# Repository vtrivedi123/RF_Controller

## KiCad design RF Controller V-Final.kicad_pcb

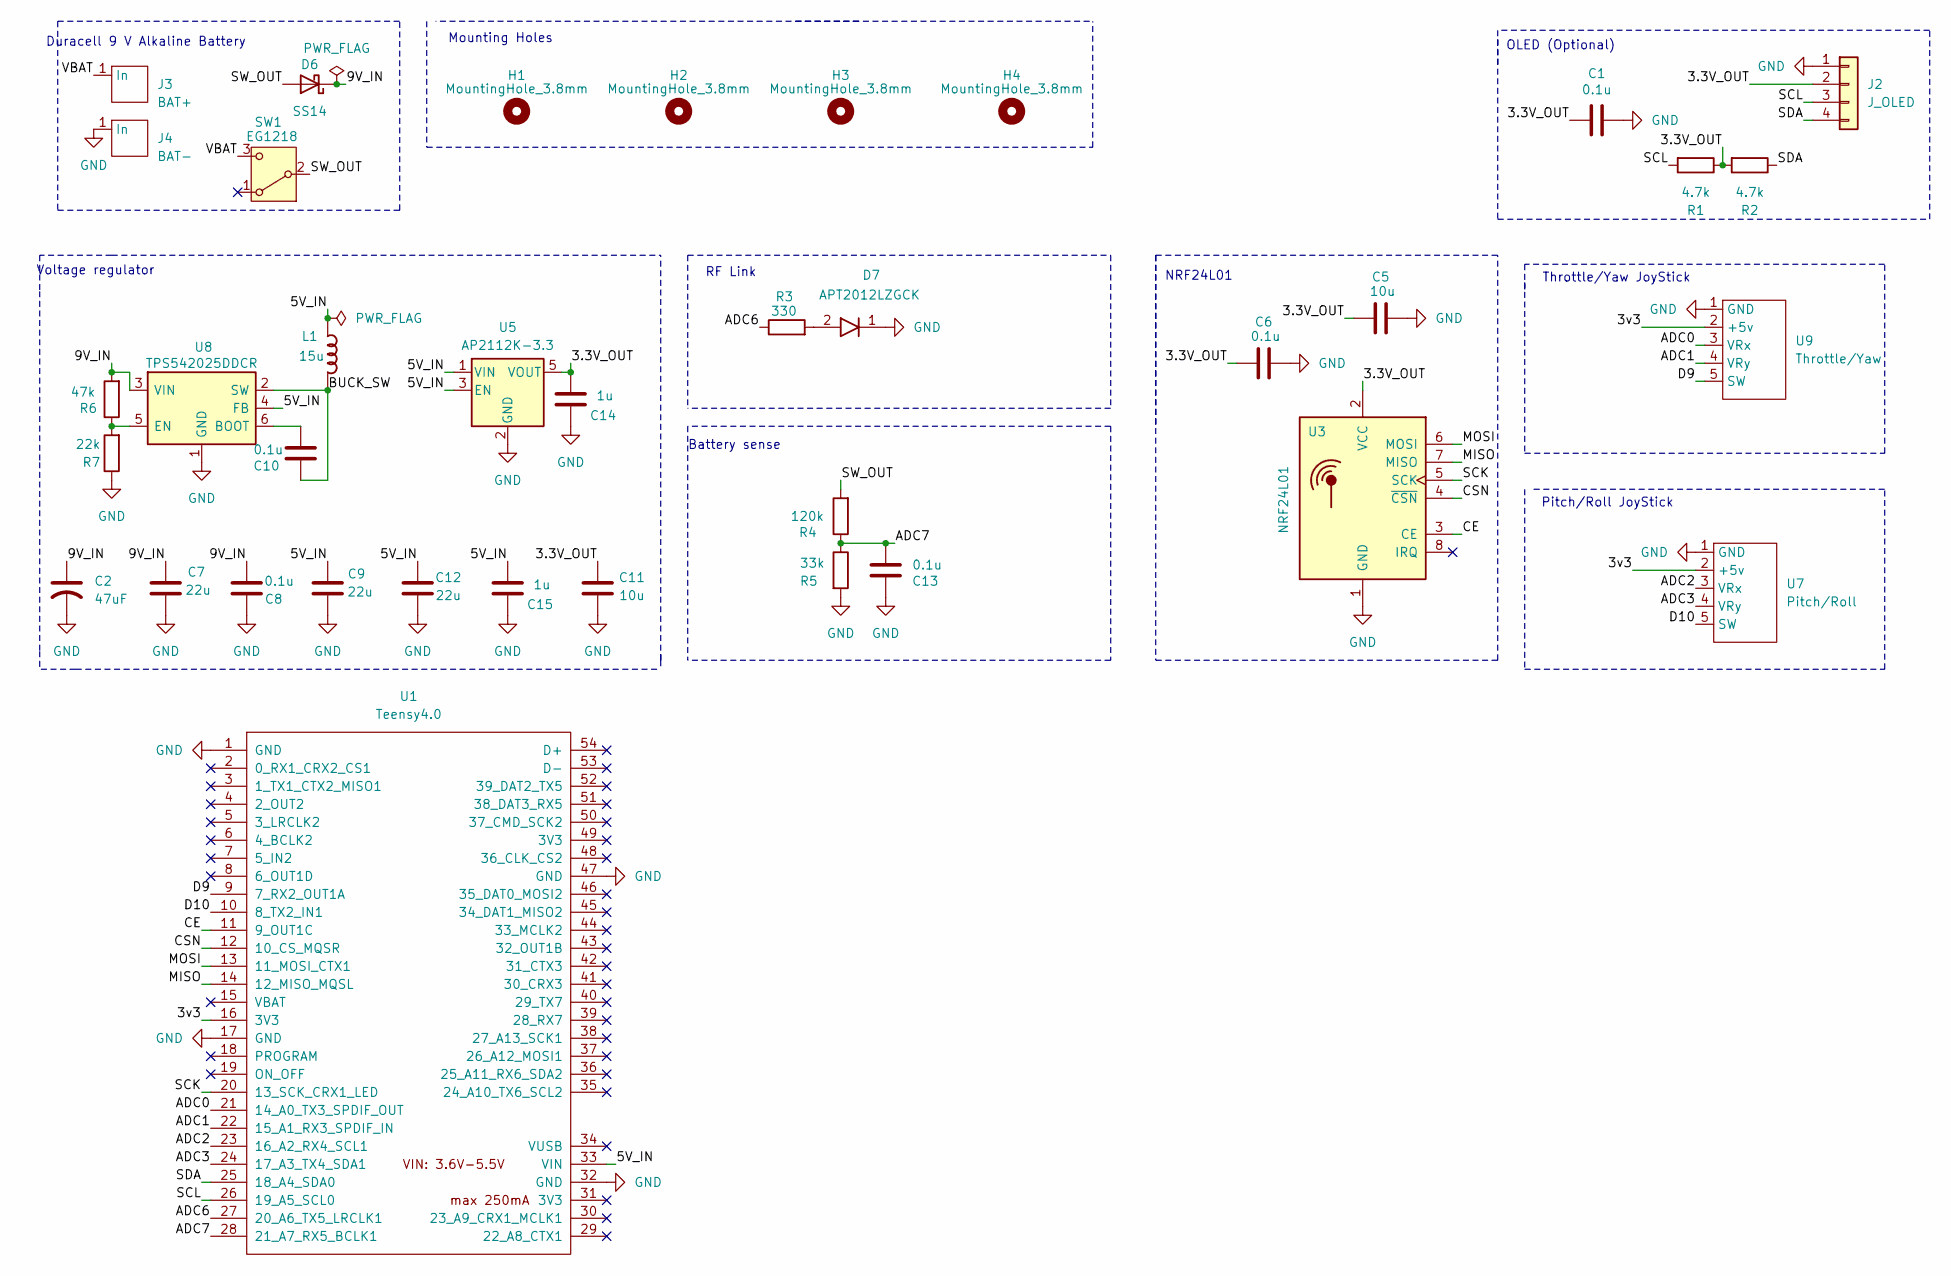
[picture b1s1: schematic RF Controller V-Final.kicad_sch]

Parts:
C1, C6, C8, C10, C13: 0.1u; C_0805_2012Metric_Pad1.18x1.45mm_HandSolder
C2: 47uF; CP_Wurth_WCAP-ASLI-D6.3L5.5
C5, C11: 10u; C_1206_3216Metric_Pad1.33x1.80mm_HandSolder
C7, C9, C12: 22u; C_1210_3225Metric_Pad1.33x2.70mm_HandSolder
C14, C15: 1u; C_0805_2012Metric_Pad1.18x1.45mm_HandSolder
D6: SS14; D_SMA
D7: APT2012LZGCK; LED_0805_2012Metric_Pad1.15x1.40mm_HandSolder
H1, H2, H3, H4: MountingHole_3.8mm
J2: J_OLED; OLED_0.96in_SSD1306_I2C_27x27mm_TOP_HEADER_SIMPLE
J3: BAT+; Pad_01
J4: BAT-; Pad_01
L1: 15u; Bourns_SRP5030HMCT
R1, R2: 4.7k; R_0805_2012Metric_Pad1.20x1.40mm_HandSolder
R3: 330; R_0805_2012Metric_Pad1.20x1.40mm_HandSolder
R4: 120k; R_0805_2012Metric_Pad1.20x1.40mm_HandSolder
R5: 33k; R_0805_2012Metric_Pad1.20x1.40mm_HandSolder
R6: 47k; R_0805_2012Metric_Pad1.20x1.40mm_HandSolder
R7: 22k; R_0805_2012Metric_Pad1.20x1.40mm_HandSolder
SW1: EG1218; SW_ES_EG1218
U1: Teensy4.0; Teensy40
U3: NRF24L01; nRF24L01_Breakout
U5: AP2112K-3.3; SOT-23-5
U7: Pitch/Roll; JOY1
U8: TPS542025DDCR; TSOT-23-6_HandSoldering
U9: Throttle/Yaw; JOY1

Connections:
/3.3V_OUT: C1.1, C5.1, C6.1, C11.1, C14.1, J2.2, R1.1, R2.2, U3.2 (VCC), U5.5 (VOUT)
/3v3: U1.16 (3V3), U7.2 (+5v), U9.2 (+5v)
/5V_IN: C9.1, C12.1, C15.2, L1.2, U1.33 (VIN), U5.1 (VIN), U5.3 (EN), U8.4 (FB)
/9V_IN: C2.1, C7.1, C8.2, D6.1 (K), R6.2, U8.3 (VIN)
/ADC0: U1.21 (14_A0_TX3_SPDIF_OUT), U9.3 (VRx)
/ADC1: U1.22 (15_A1_RX3_SPDIF_IN), U9.4 (VRy)
/ADC2: U1.23 (16_A2_RX4_SCL1), U7.3 (VRx)
/ADC3: U1.24 (17_A3_TX4_SDA1), U7.4 (VRy)
/ADC6: R3.1, U1.27 (20_A6_TX5_LRCLK1)
/ADC7: C13.1, R4.1, R5.1, U1.28 (21_A7_RX5_BCLK1)
/BUCK_SW: C10.1, L1.1, U8.2 (SW)
/CE: U1.11 (9_OUT1C), U3.3 (CE)
/CSN: U1.12 (10_CS_MQSR), U3.4 (~CSN)
/D9: U1.9 (7_RX2_OUT1A), U9.5 (SW)
/D10: U1.10 (8_TX2_IN1), U7.5 (SW)
/MISO: U1.14 (12_MISO_MQSL), U3.7 (MISO)
/MOSI: U1.13 (11_MOSI_CTX1), U3.6 (MOSI)
/SCK: U1.20 (13_SCK_CRX1_LED), U3.5 (SCK)
/SCL: J2.3, R1.2, U1.26 (19_A5_SCL0)
/SDA: J2.4, R2.1, U1.25 (18_A4_SDA0)
/SW_OUT: D6.2 (A), R4.2, SW1.2 (B)
/VBAT: J3.1 (In_1), SW1.3 (C)
GND: C1.2, C2.2, C5.2, C6.2, C7.2, C8.1, C9.2, C11.2, C12.2, C13.2, C14.2, C15.1, D7.1 (K), J2.1, J4.1 (In_1), R5.2, R7.1, U1.1 (GND), U1.17 (GND), U1.32 (GND), U1.47 (GND), U3.1 (GND), U5.2 (GND), U7.1 (GND), U8.1 (GND), U9.1 (GND)
unnamed: D7.2 (A), R3.2
unnamed: C10.2, U8.6 (BOOT)
unnamed: R6.1, R7.2, U8.5 (EN)

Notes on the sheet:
Battery sense
Throttle/Yaw JoyStick
OLED (Optional)
RF Link
Pitch/Roll JoyStick
Duracell 9 V Alkaline Battery
Voltage regulator
Mounting Holes
NRF24L01

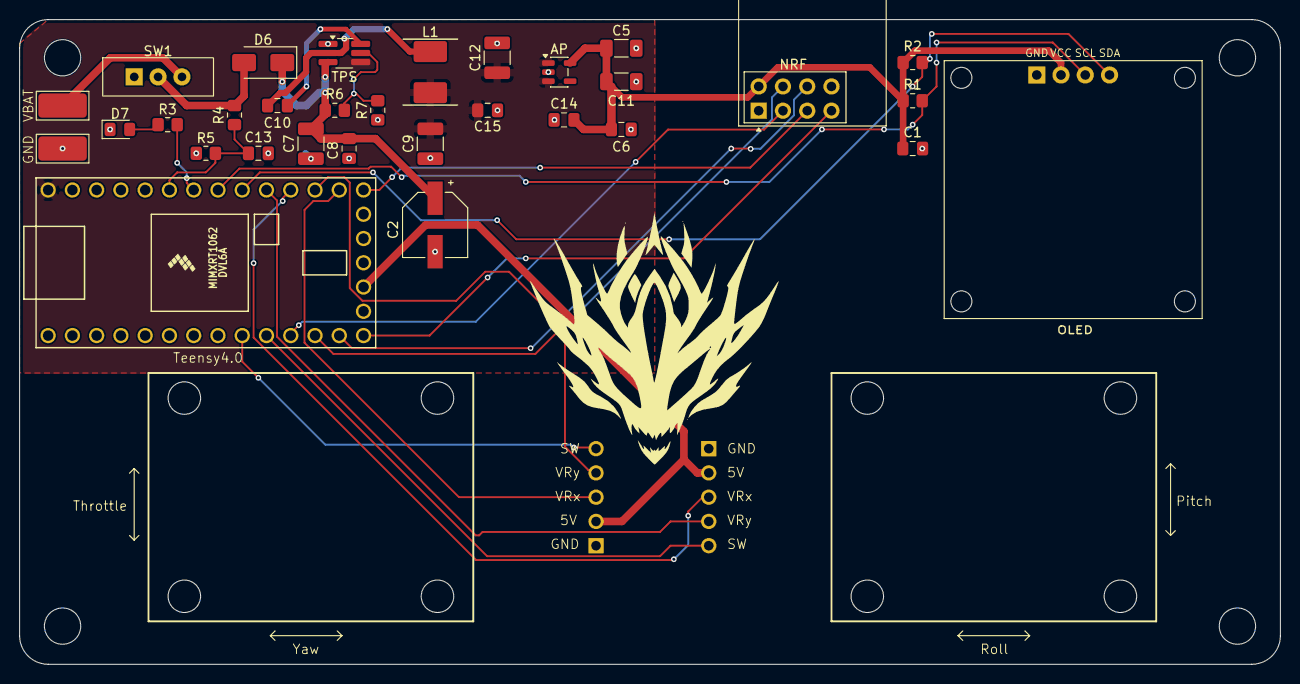
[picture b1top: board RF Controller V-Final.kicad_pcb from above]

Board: 2 copper layers, 132.0 x 67.5 mm, 37 parts (0 on the bottom side), 26 nets.
